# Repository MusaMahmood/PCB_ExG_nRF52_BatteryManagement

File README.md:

# PCB_ExG_nRF52_BatteryManagement

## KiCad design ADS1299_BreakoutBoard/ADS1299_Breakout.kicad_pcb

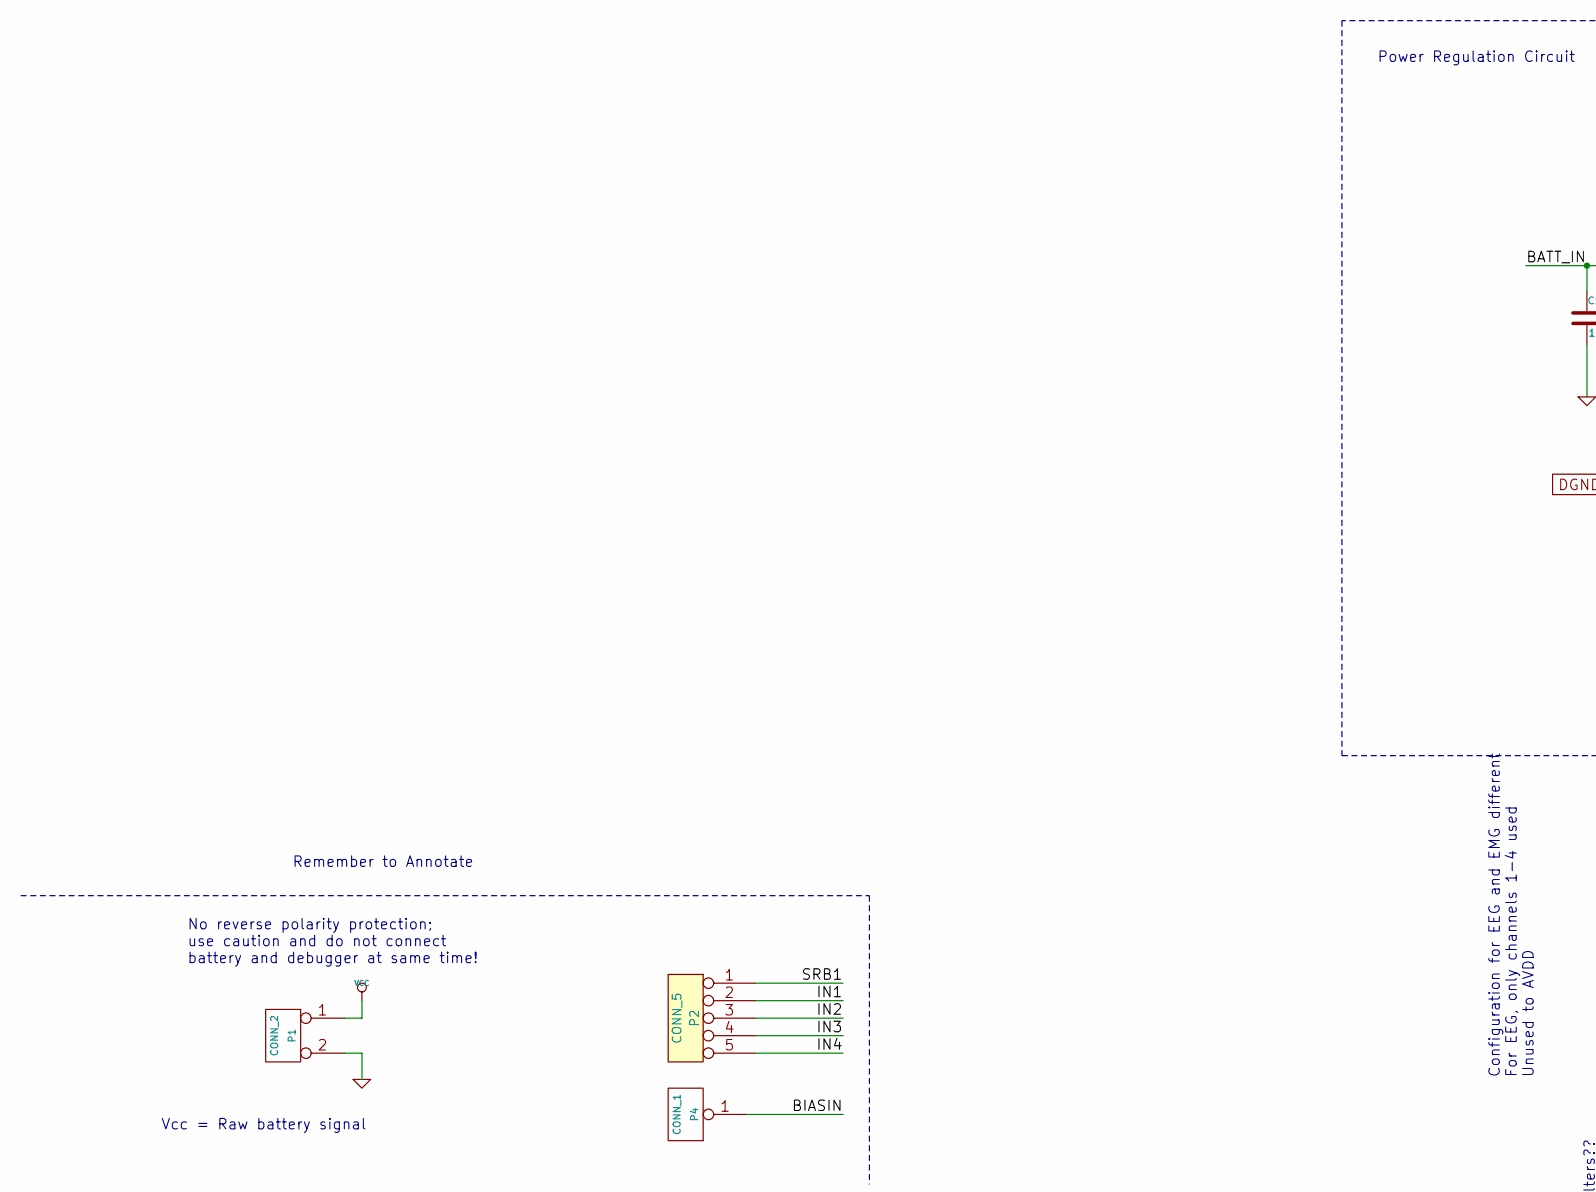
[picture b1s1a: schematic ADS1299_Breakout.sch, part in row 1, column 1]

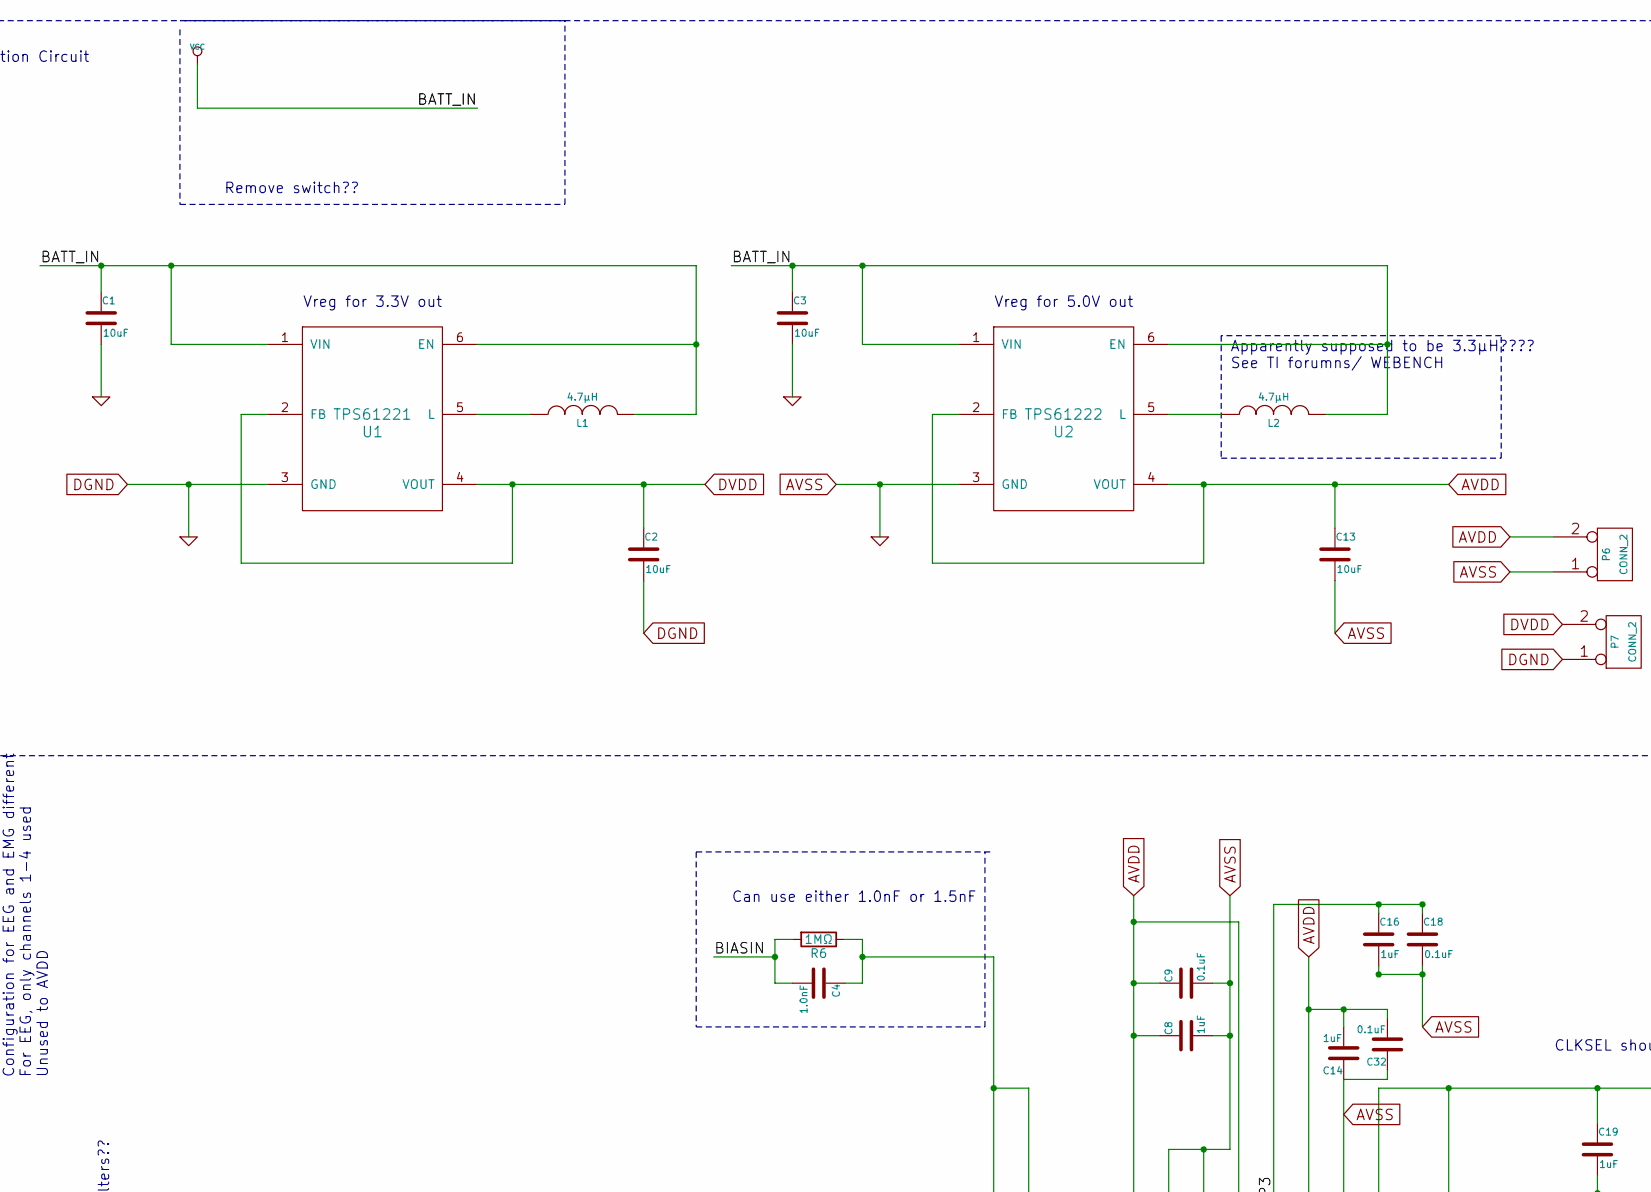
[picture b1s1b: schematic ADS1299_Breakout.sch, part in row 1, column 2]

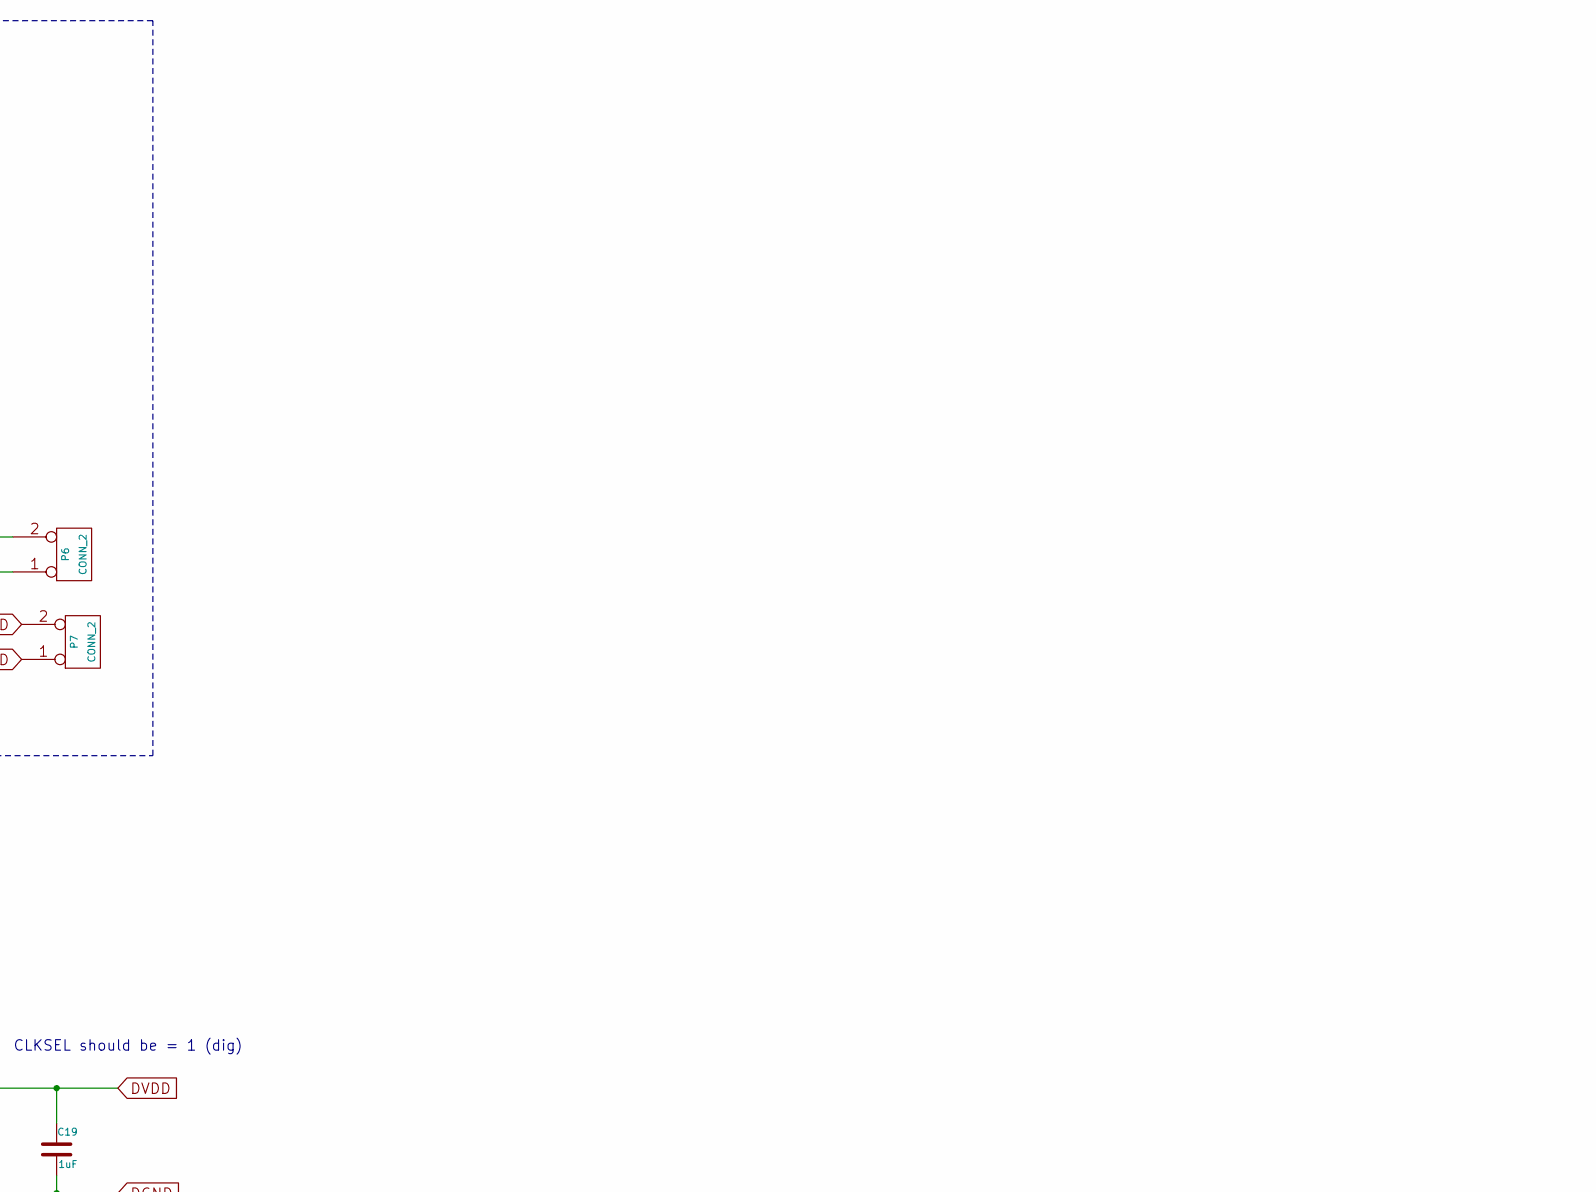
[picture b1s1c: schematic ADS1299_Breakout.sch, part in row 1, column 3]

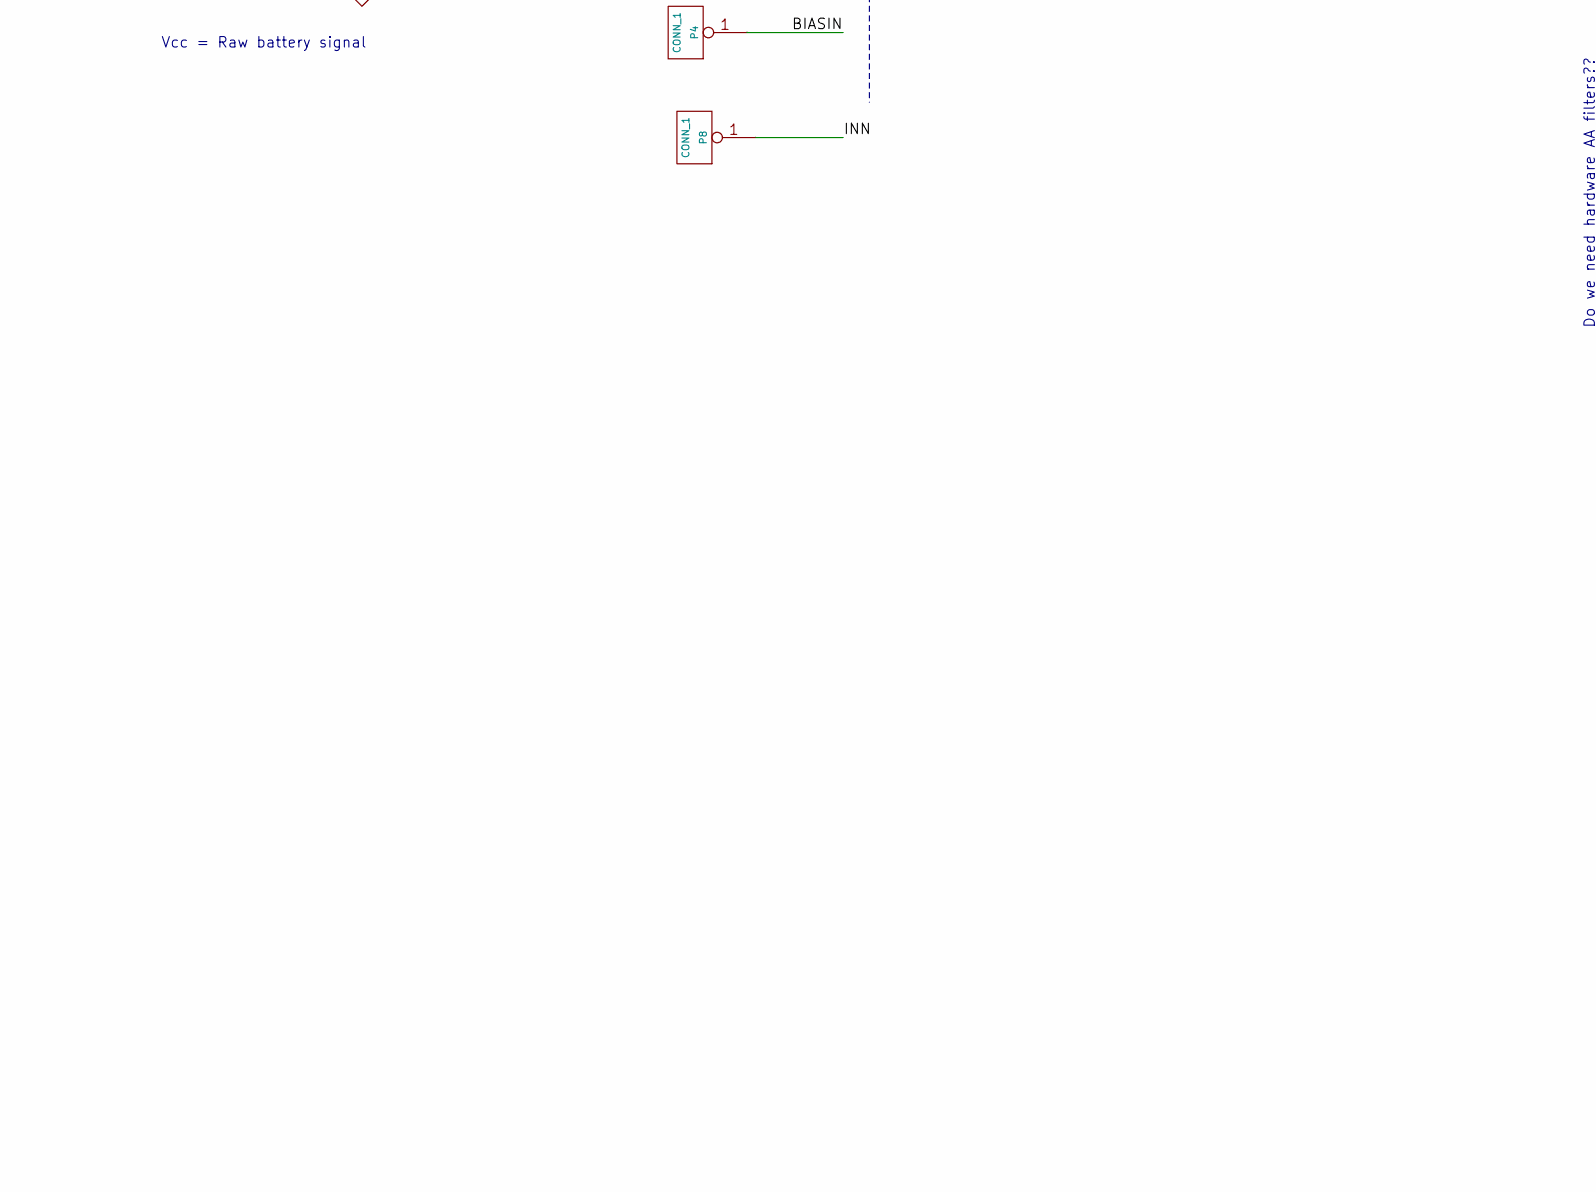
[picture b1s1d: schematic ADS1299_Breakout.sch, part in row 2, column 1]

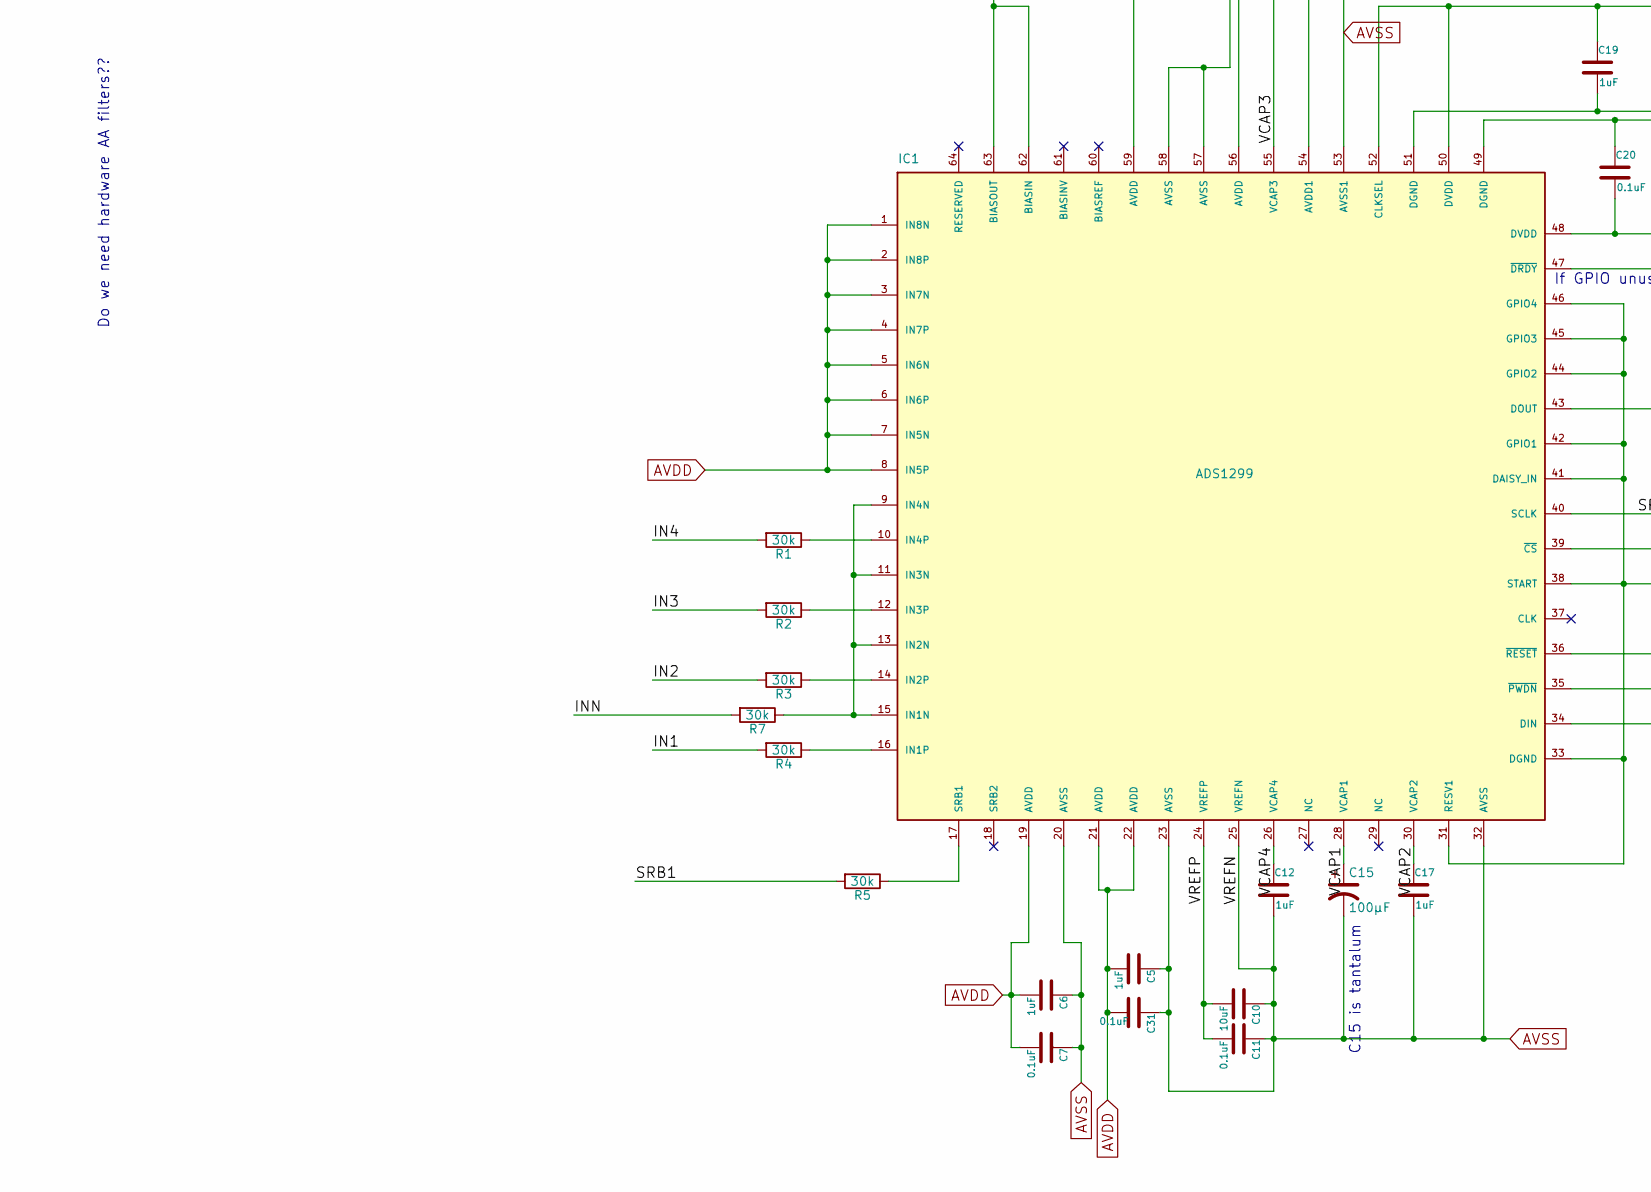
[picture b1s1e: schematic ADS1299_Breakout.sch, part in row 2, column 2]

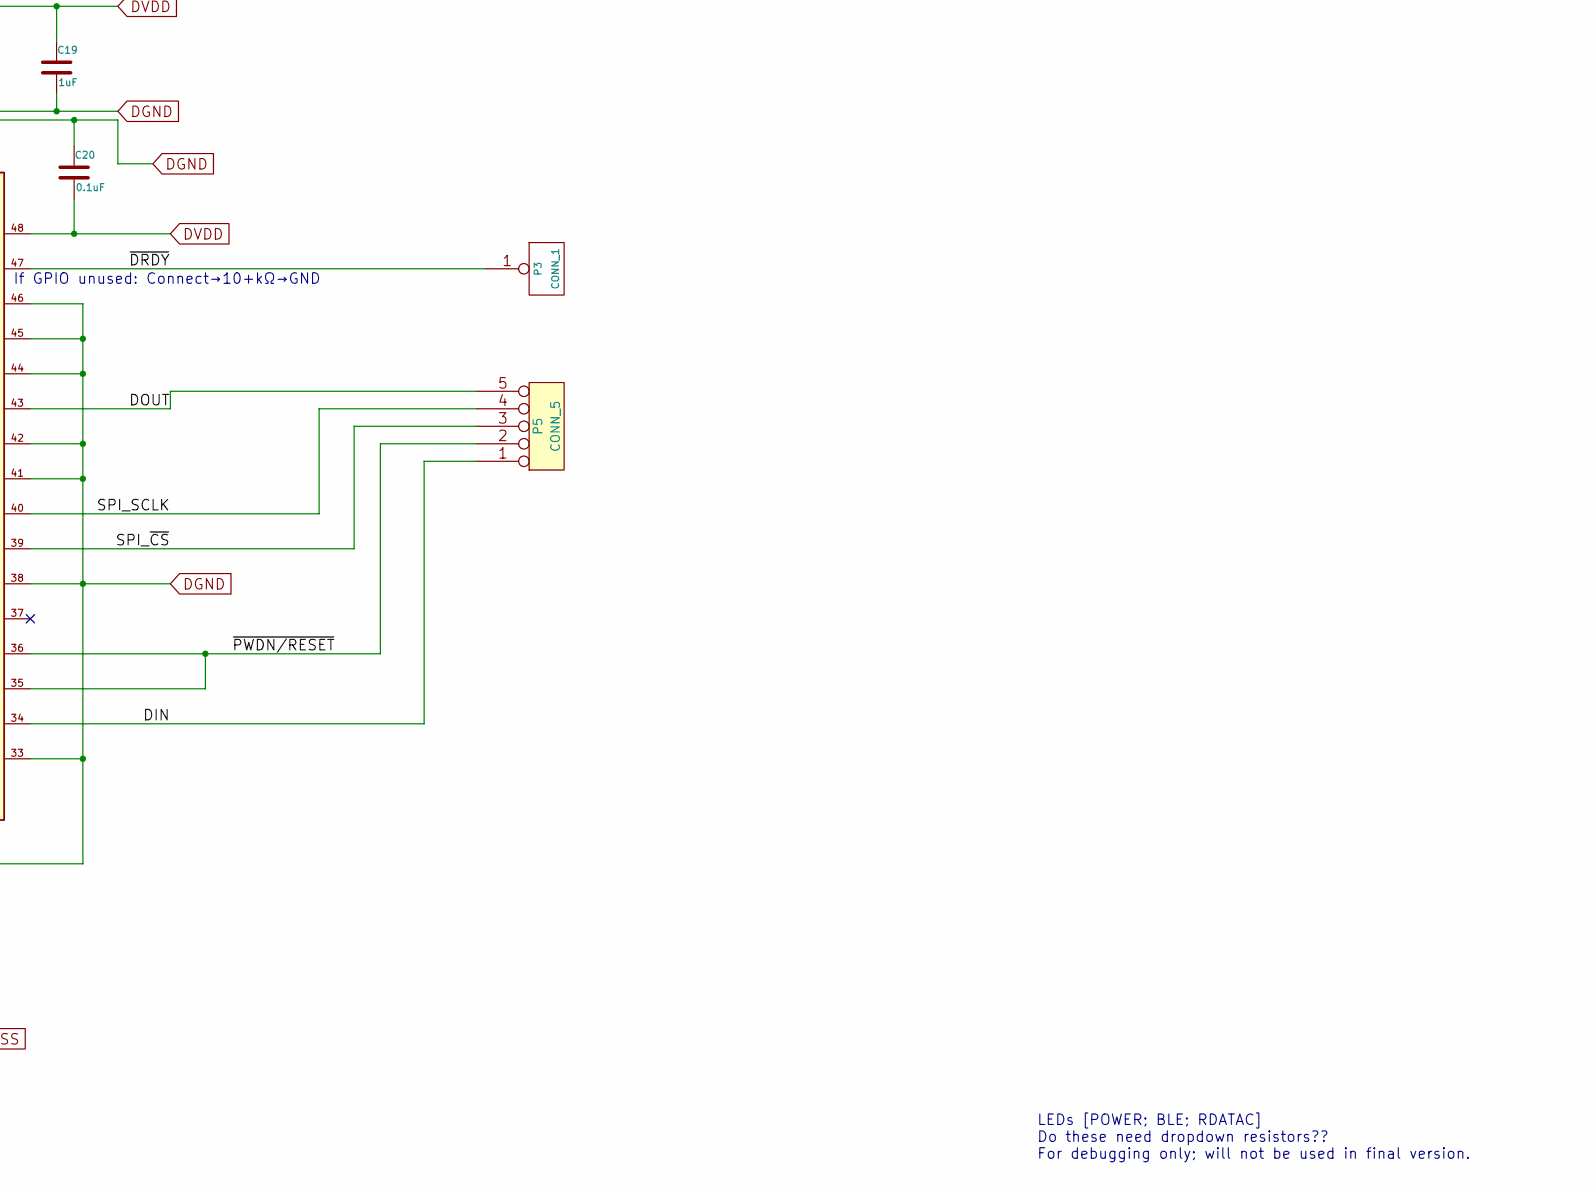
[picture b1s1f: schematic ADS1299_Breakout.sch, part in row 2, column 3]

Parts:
C1, C2, C3, C10, C13: 10uF
C4: 1.0nF
C5, C6, C8, C12, C14, C16, C17, C19: 1uF
C7, C9, C11, C18, C20, C31, C32: 0.1uF
C15: 100µF
IC1: ADS1299
L1, L2: 4.7µH
P1, P6, P7: CONN_2
P2, P5: CONN_5
P3, P4, P8: CONN_1
R1, R2, R3, R4, R5, R7: 30k
R6: 1MΩ
U1: TPS61221
U2: TPS61222

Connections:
/BIASIN: C4.2, P4.1, R6.2
/DIN: IC1.34 (DIN), P5.1
/DOUT: IC1.43 (DOUT), P5.5
/IN1: P2.2, R4.2
/IN2: P2.3, R3.2
/IN3: P2.4, R2.2
/IN4: P2.5, R1.2
/INN: P8.1, R7.2
/SPI_SCLK: IC1.40 (SCLK), P5.4
/SPI_~CS: IC1.39 (~CS), P5.3
/SRB1: P2.1, R5.2
/VCAP1: C15.1, IC1.28 (VCAP1)
/VCAP2: C17.1, IC1.30 (VCAP2)
/VCAP3: C16.1, C18.1, IC1.55 (VCAP3)
/VCAP4: C12.1, IC1.26 (VCAP4)
/VREFP: C10.2, C11.2, IC1.24 (VREFP)
/~DRDY: IC1.47 (~DRDY), P3.1
/~PWDN/RESET: IC1.35 (~PWDN), IC1.36 (~RESET), P5.2
AVDD: C5.2, C6.2, C7.2, C8.1, C9.1, C13.1, C14.2, C31.2, C32.2, IC1.1 (IN8N), IC1.2 (IN8P), IC1.3 (IN7N), IC1.4 (IN7P), IC1.5 (IN6N), IC1.6 (IN6P), IC1.7 (IN5N), IC1.8 (IN5P), IC1.19 (AVDD), IC1.21 (AVDD), IC1.22 (AVDD), IC1.54 (AVDD1), IC1.56 (AVDD), IC1.59 (AVDD), P6.2 (PM), U2.2 (FB), U2.4 (VOUT)
AVSS: C1.2, C2.2, C3.2, C5.1, C6.1, C7.1, C8.2, C9.2, C10.1, C11.1, C12.2, C13.2, C14.1, C15.2, C16.2, C17.2, C18.2, C19.2, C20.1, C31.1, C32.1, IC1.20 (AVSS), IC1.23 (AVSS), IC1.25 (VREFN), IC1.31 (RESV1), IC1.32 (AVSS), IC1.33 (DGND), IC1.38 (START), IC1.41 (DAISY_IN), IC1.42 (GPIO1), IC1.44 (GPIO2), IC1.45 (GPIO3), IC1.46 (GPIO4), IC1.49 (DGND), IC1.51 (DGND), IC1.53 (AVSS1), IC1.57 (AVSS), IC1.58 (AVSS), P1.2 (PM), P6.1, P7.1, U1.3 (GND), U2.3 (GND)
DVDD: C2.1, C19.1, C20.2, IC1.48 (DVDD), IC1.50 (DVDD), IC1.52 (CLKSEL), P7.2 (PM), U1.2 (FB), U1.4 (VOUT)
unnamed: C4.1, IC1.62 (BIASIN), IC1.63 (BIASOUT), R6.1
unnamed: IC1.10 (IN4P), R1.1
unnamed: IC1.9 (IN4N), IC1.11 (IN3N), IC1.13 (IN2N), IC1.15 (IN1N), R7.1
unnamed: IC1.12 (IN3P), R2.1
unnamed: IC1.14 (IN2P), R3.1
unnamed: IC1.16 (IN1P), R4.1
unnamed: IC1.17 (SRB1), R5.1
unnamed: L1.1, U1.5 (L)
unnamed: L2.1, U2.5 (L)
VCC: C1.1, C3.1, L1.2, L2.2, P1.1, U1.1 (VIN), U1.6 (EN), U2.1 (VIN), U2.6 (EN)

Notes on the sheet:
No reverse polarity protection; use caution and do not connect battery and debugger at same time!
Can use either 1.0nF or 1.5nF
Configuration for EEG and EMG different For EEG, only channels 1-4 used Unused to AVDD
Do we need hardware AA filters??
Vreg for 3.3V out
Remember to Annotate
If GPIO unused: Connect→10+kΩ→GND
Vreg for 5.0V out
LEDs [POWER; BLE; RDATAC] Do these need dropdown resistors?? For debugging only; will not be used in final version.
Power Regulation Circuit
CLKSEL should be = 1 (dig)
C15 is tantalum
Apparently supposed to be 3.3µH???? See TI forumns/ WEBENCH
Remove switch??
Vcc = Raw battery signal

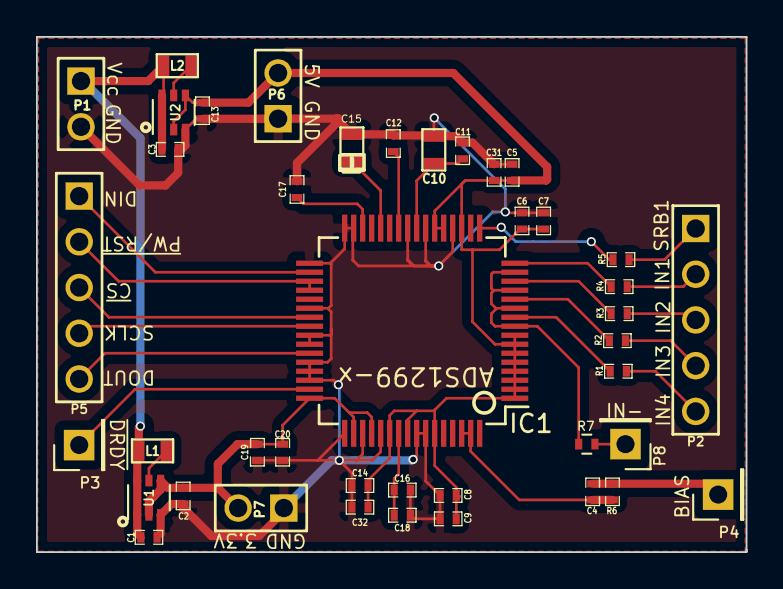
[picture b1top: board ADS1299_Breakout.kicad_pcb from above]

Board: 2 copper layers, 39.4 x 28.6 mm, 42 parts (0 on the bottom side), 31 nets.

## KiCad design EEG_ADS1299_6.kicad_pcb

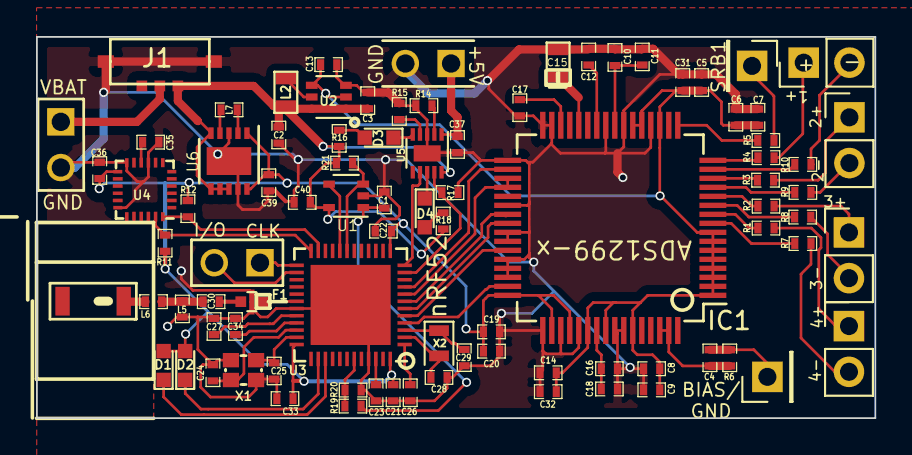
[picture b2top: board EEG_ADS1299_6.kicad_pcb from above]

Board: 2 copper layers, 46.6 x 21.2 mm, 88 parts (0 on the bottom side), 71 nets.

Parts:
A1: CHIP-ANT; JTI-2450AT18A100-CHIP-ANT
C1, C2, C3, C10, C13, C40: 10uF; SM0402
C4: 1.0nF; SM0402
C5, C6, C8, C12, C14, C16, C17, C19, C37: 1uF; SM0402
C7, C9, C11, C18, C20, C31, C32: 0.1uF; SM0402
C15: 100µF; SM0603_Tant
C21: 4.7µF; SM0402
C22, C26, C33, C35, C36: 100nF; SM0402
C23: 1.0µF; SM0402
C24, C25, C28, C29: 12pF; SM0402
C27: N.C.; SM0402
C30: 1.0pF; SM0402
C34: 100pF; SM0402
C39: 22uF; SM0402
D1, D2, D3, D4: LED; LED_0603
F1: 2450FM07A0029; R_0402
IC1: ADS1299; TQFP-64_10x10mm_Pitch0.5mm
J1: CONN_01X05; SSAJ1201
L2: 4.7µH; SM0603
L5: 2.7nH; SM0402
L6: 3.9nH; SM0402
L7: 2.20µH; SM0402
P1, P2, P6: CONN_2; PIN_ARRAY_2X1
P3, P4: CONN_1; Pin_Header_Straight_1x01_Pitch2.54mm
P7, P8, P9, P10: CONN_01X02; Pin_Header_Straight_1x02_Pitch2.54mm
R1, R2, R3, R4, R5, R7, R8, R9, R10: 30k; SM0402
R6: 1MΩ; SM0402
R11, R12, R17, R21: 10k; SM0402
R14: 1k; SM0402
R15: 2k; SM0402
R16, R18: 1.5k; SM0402
R19, R20: 1M; SM0402
U1: TPS2294x; SOT-353_SC-70-5
U2: TPS61222; SOT-363_SC-70-6
U3: NRF528XX-QFAA; UQFN-48-1EP_6x6mm_Pitch0.4mm
U4: MPU-9250; QFN-24_3x3mm_Pitch0.4mm
U5: BQ24045; DFN-10_2x2mm_Pitch0.4mm
U6: TPS63001; DFN-10-1EP_3x3mm_Pitch0.5mm
X1: Crystal_GND24; CRYSTAL-SMD-2.0MMx1.6MM
X2: 32.768 kHz; Crystal_SMD_2012-2pin_2.0x1.2mm

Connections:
/BATT_ADC_AIN: R19.2, R20.1, U3.43
/BIASIN: C4.2, P4.1, R6.2
/DC+INPUT: C37.2, P6.1, U5.1
/DEC1: C26.1, U3.1
/DEC2: C27.1, U3.32
/DEC3: C34.1, U3.33
/DEC4: C23.1, U3.46
/DIN: IC1.34, U3.9
/DOUT: IC1.43, U3.5
/GPIO_CTRL_PWR_ON: U1.4, U3.20
/GPIO_ISET: U3.12, U5.7
/GPIO_OVERCURRENT: R21.2, U1.3, U3.19
/GPIO_TTDM_BAT_EN: R17.2, U3.11, U5.9
/IN1: P7.1, R4.2
/IN1-: P7.2, R10.2
/IN2: P8.1, R3.2
/IN2-: P8.2, R9.2
/IN3: P9.1, R2.2
/IN3-: P9.2, R8.2
/IN4: P10.1, R1.2
/IN4-: P10.2, R7.2
/LED2: D1.1, U3.39
/LED3: D2.1, U3.38
/RF: C30.1, F1.4
/SCL: R11.2, U3.24, U4.23
/SDI: R12.2, U3.23, U4.24
/SPI_SCLK: IC1.40, U3.6
/SPI_~CS: IC1.39, U3.7
/SRB1: P3.1, R5.2
/SWDCLK: P2.1, U3.25
/SWDIO: P2.2, U3.26
/VCAP1: C15.1, IC1.28
/VCAP2: C17.1, IC1.30
/VCAP3: C16.1, C18.1, IC1.55
/VCAP4: C12.1, IC1.26
/VREFP: C10.2, C11.2, IC1.24
/~DRDY: IC1.47, U3.4
/~PWDN/RESET: IC1.35, IC1.36, U3.8
AVDD: C5.2, C6.2, C7.2, C8.1, C9.1, C13.1, C14.2, C31.2, C32.2, IC1.1, IC1.2, IC1.3, IC1.4, IC1.5, IC1.6, IC1.7, IC1.8, IC1.19, IC1.21, IC1.22, IC1.54, IC1.56, IC1.59, U2.2, U2.4
AVSS: C1.2, C2.2, C3.2, C5.1, C6.1, C7.1, C8.2, C9.2, C10.1, C11.1, C12.2, C13.2, C14.1, C15.2, C16.2, C17.2, C18.2, C19.2, C20.1, C21.1, C22.2, C23.2, C24.1, C25.1, C26.2, C27.2, C28.2, C29.2, C31.1, C32.1, C33.1, C34.2, C35.2, C36.2, C37.1, C39.2, C40.2, F1.1, F1.3, IC1.20, IC1.23, IC1.25, IC1.31, IC1.32, IC1.33, IC1.38, IC1.41, IC1.42, IC1.44, IC1.45, IC1.46, IC1.49, IC1.51, IC1.53, IC1.57, IC1.58, J1.4, J1.5, L5.2, P1.2, P6.2, R14.1, R15.1, R17.1, R20.2, U1.2, U2.3, U3.31, U3.45, U3.49, U4.9, U4.12, U4.18, U5.3, U5.11, U6.3, U6.9, U6.11, X1.2, X1.4
DVDD: C19.1, C20.2, C21.2, C22.1, C33.2, C36.1, C39.1, D1.2, D2.2, IC1.48, IC1.50, IC1.52, R11.1, R12.1, U3.13, U3.36, U3.48, U4.13, U6.1, U6.10
unnamed: A1.1, L6.2
unnamed: C1.1, R19.1, U1.1
unnamed: C4.1, IC1.62, IC1.63, R6.1
unnamed: C24.2, U3.34, X1.1
unnamed: C25.2, U3.35, X1.3
unnamed: C28.1, U3.2, X2.2
unnamed: C29.1, U3.3, X2.1
unnamed: C30.2, L5.1, L6.1
unnamed: C35.1, U4.10
unnamed: D3.1, U5.5
unnamed: D3.2, R16.2
unnamed: D4.1, U5.8
unnamed: D4.2, R18.1
unnamed: F1.2, U3.30
unnamed: IC1.9, R7.1
unnamed: IC1.10, R1.1
unnamed: IC1.11, R8.1
unnamed: IC1.12, R2.1
unnamed: IC1.13, R9.1
unnamed: IC1.14, R3.1
unnamed: IC1.15, R10.1
unnamed: IC1.16, R4.1
unnamed: IC1.17, R5.1
unnamed: L2.1, U2.5
unnamed: L7.1, U6.4
unnamed: L7.2, U6.2
unnamed: R14.2, U5.2
unnamed: R15.2, U5.4
VCC: J1.2, P1.1
VCC_SW: C2.1, C3.1, C40.1, J1.1, L2.2, R16.1, R18.2, R21.1, U1.5, U2.1, U2.6, U5.10, U6.5, U6.6, U6.7, U6.8

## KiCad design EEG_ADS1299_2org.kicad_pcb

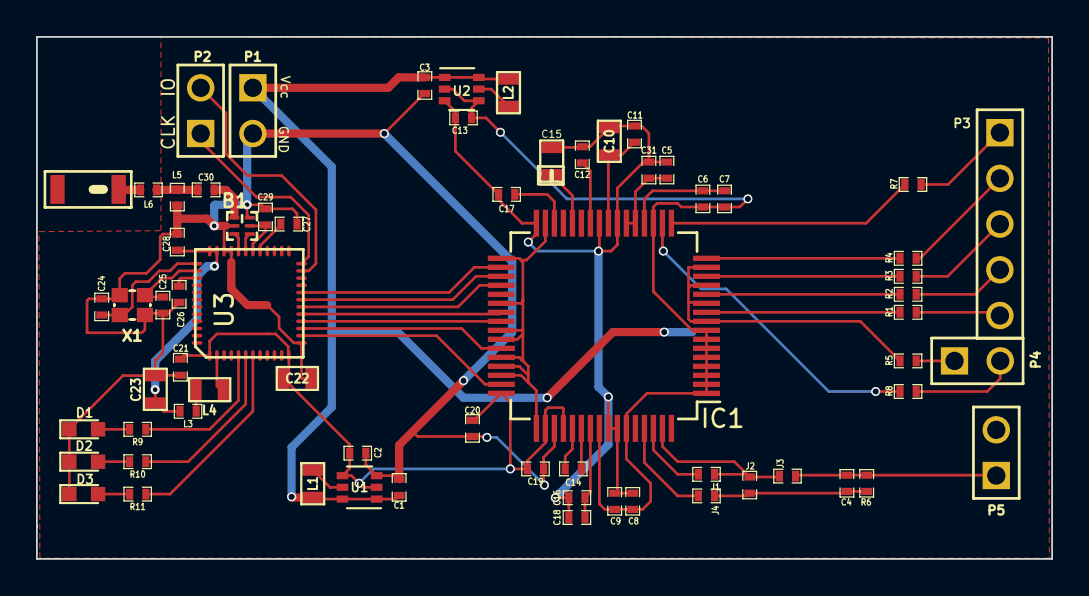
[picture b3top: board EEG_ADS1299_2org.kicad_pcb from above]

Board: 2 copper layers, 56.4 x 29.0 mm, 68 parts (1 on the bottom side), 62 nets.

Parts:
A1: CHIP-ANT; JTI-2450AT18A100-CHIP-ANT
B1: 2450BM14E0003
C1, C2, C3, C13: 10uF; SM0402
C4: 1.0nF; SM0402
C5, C6, C8, C12, C14, C16, C17, C19, C20: 1uF; SM0402
C7, C9, C11, C18, C31: 0.1uF; SM0402
C10: 10uF; SM0603
C15: 100µF; SM0603_Tant
C21: 4.7uF; SM0402
C22: 100nF; SM0603
C23: 1uF; SM0603
C24, C25: 12pF 2%; SM0402
C26: 100nF; SM0402
C27: 47nF; SM0402
C28: 1nF; SM0402
C29: 2.2nF; SM0402
C30: 1.0pF; SM0402
D1, D2, D3: LED; LED_0603
IC1: ADS1299; TQFP-64_10x10mm_Pitch0.5mm
J1, J2, J3, J4: 0; SM0402
L1, L2: 4.7µH; SM0603
L3: 15nH; SM0402
L4: 10uH; SM0603
L5: 2.7nH; SM0402
L6: 3.9nH; SM0402
P1, P2, P4, P5: CONN_2; PIN_ARRAY_2X1
P3: CONN_5; PIN_ARRAY_5x1
P6: PWR; 3012TR-CR1632
R1, R2, R3, R4, R5, R7, R8: 30k; SM0402
R6: 1MΩ; SM0402
R9, R10, R11: R; SM0402
U1: TPS61221; SOT-363_SC-70-6
U2: TPS61222; SOT-363_SC-70-6
U3: NRF51X22-QFN; QFN48-6X6
X1: 16MHz; CRYSTAL-SMD-2.0MMx1.6MM

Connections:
/ANT1: B1.4, U3.31
/ANT2: B1.3, U3.32
/BIASIN: C4.2, J3.2, P5.1, R6.2
/DCC: L4.1, U3.2
/DEC1: C26.1, U3.39
/DEC2: C27.1, U3.29
/DIN: IC1.34, U3.20
/DOUT: IC1.43, U3.15
/IN1: P3.2, R4.2
/IN2: P3.3, R3.2
/IN3: P3.4, R2.2
/IN4: P3.5, R1.2
/INN: P4.1, R5.2
/RF: B1.1, C30.1
/SPI_SCLK: IC1.40, U3.16
/SPI_~CS: IC1.39, U3.17
/SRB1: P3.1, R7.2
/SRB2: P4.2, R8.2
/SWDCLK: P2.1, U3.24
/SWDIO: P2.2, U3.23
/VDD_PA: B1.5, C29.1, U3.30
/XC1: C24.2, U3.37, X1.1
/XC2: C25.2, U3.38, X1.3
/~DRDY: IC1.47, U3.14
/~PWDN: IC1.35, U3.19
/~RESET: IC1.36, U3.18
AVDD: C6.2, C7.2, C8.1, C9.1, C13.1, IC1.1, IC1.2, IC1.3, IC1.4, IC1.5, IC1.6, IC1.7, IC1.8, IC1.19, IC1.56, IC1.59, U2.2, U2.4
AVSS: B1.2, B1.6, C1.2, C2.2, C3.2, C5.1, C8.2, C9.2, C10.1, C11.1, C12.2, C13.2, C15.2, C16.2, C17.2, C18.2, C19.2, C20.1, C21.2, C22.2, C23.2, C24.1, C25.1, C26.2, C27.2, C28.2, C29.2, C31.1, D1.1, D2.1, D3.1, IC1.23, IC1.25, IC1.31, IC1.32, IC1.33, IC1.38, IC1.41, IC1.42, IC1.44, IC1.45, IC1.46, IC1.49, IC1.51, IC1.57, IC1.58, L5.2, P1.2, P6.2, U1.3, U2.3, U3.13, U3.33, U3.34, X1.2, X1.4
DVDD: C2.1, C19.1, C20.2, C21.1, C22.1, IC1.48, IC1.50, IC1.52, U1.2, U1.4, U3.1, U3.12
unnamed: A1.1, L6.2
unnamed: C4.1, J2.2, J4.2, R6.1
unnamed: C6.1, C7.1, IC1.20
unnamed: C10.2, C11.2, IC1.24
unnamed: C12.1, IC1.26
unnamed: C14.1, IC1.53
unnamed: C14.2, IC1.54
unnamed: C15.1, IC1.28
unnamed: C16.1, C18.1, IC1.55
unnamed: C17.1, IC1.30
unnamed: C30.2, L5.1, L6.1
unnamed: C5.2, C31.2, IC1.21, IC1.22
unnamed: D1.2, R9.1
unnamed: D2.2, R10.1
unnamed: D3.2, R11.1
unnamed: IC1.10, R1.1
unnamed: IC1.9, IC1.11, IC1.13, IC1.15, R5.1
unnamed: IC1.12, R2.1
unnamed: IC1.14, R3.1
unnamed: IC1.16, R4.1
unnamed: IC1.17, R7.1
unnamed: IC1.18, R8.1
unnamed: IC1.61, J4.1
unnamed: IC1.62, J1.1
unnamed: IC1.63, J1.2, J2.1, J3.1
unnamed: L1.1, U1.5
unnamed: L2.1, U2.5
unnamed: L3.1, L4.2
unnamed: R9.2, U3.5
unnamed: R10.2, U3.6
unnamed: R11.2, U3.7
VAA: C23.1, C28.1, L3.2, U3.35, U3.36
VCC: C1.1, C3.1, L1.2, L2.2, P1.1, P6.1, U1.1, U1.6, U2.1, U2.6

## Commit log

2017-09-14 Initial commit of new design with battery management - PCB design incomplete.
2017-09-14 Huge update. Rough draft of device with battery management.
2017-09-14 Minor aestehtic changes to PCB. Almsot complete, requires final revision.
2017-09-21 Updated battery management design v2 complete.
2017-09-21 Done with adjustments. Needs final revision before shipping
2017-09-22 Final version, v4.
2017-09-26 Battery Management circuit. Requires revision to different ICs.
